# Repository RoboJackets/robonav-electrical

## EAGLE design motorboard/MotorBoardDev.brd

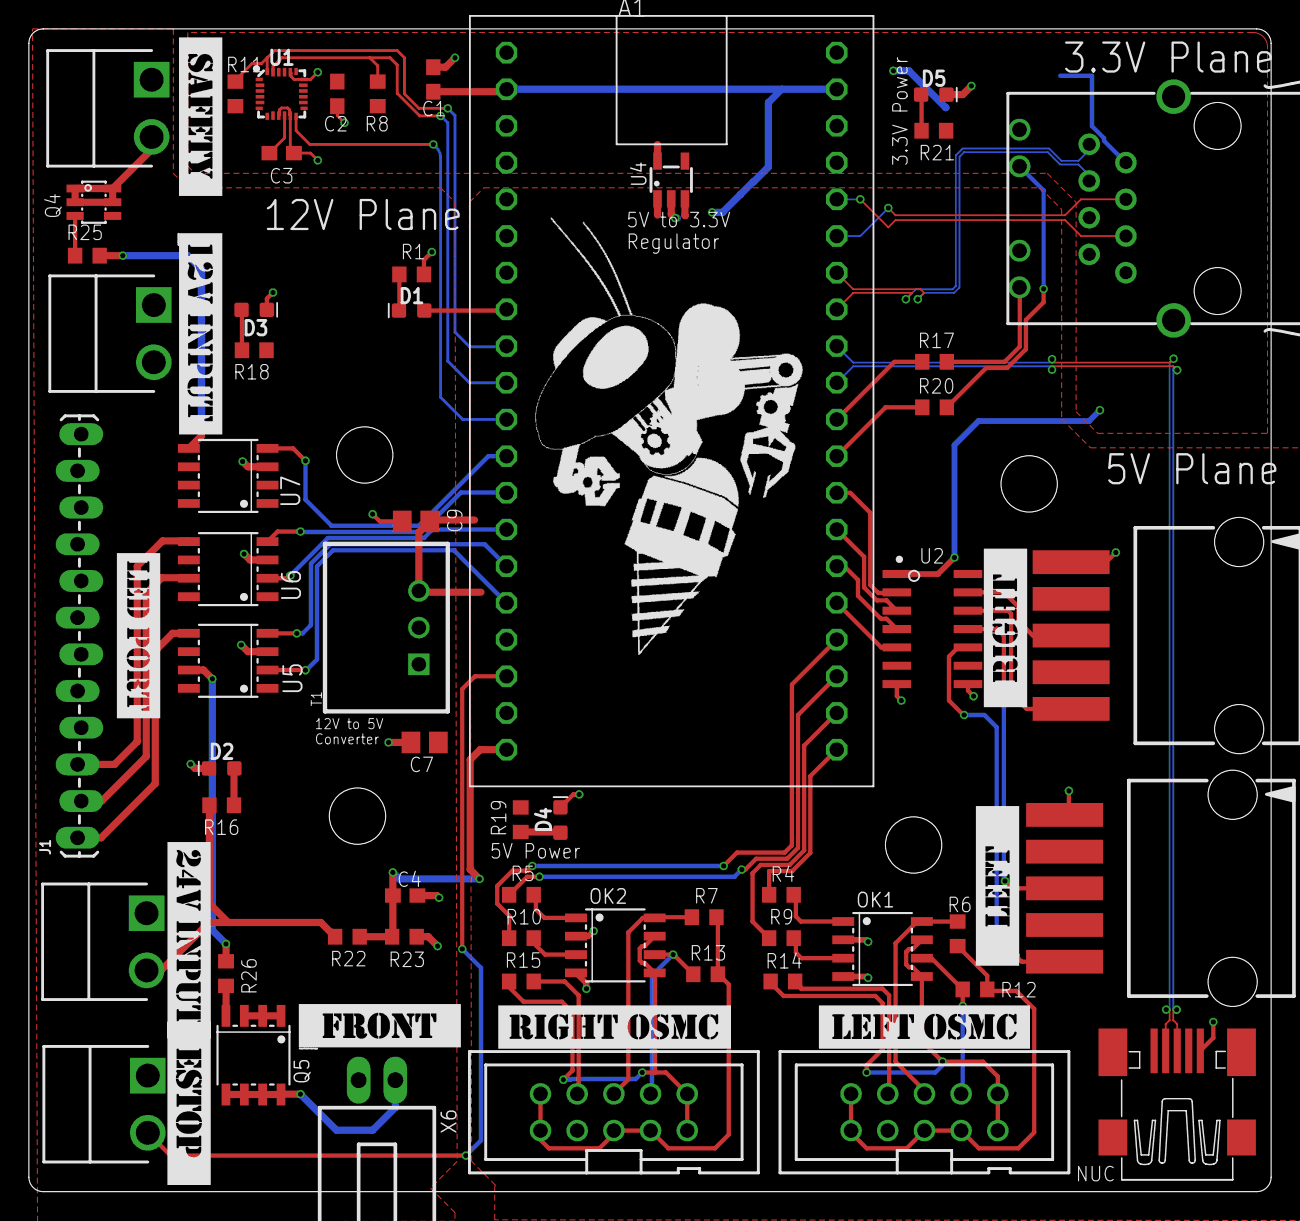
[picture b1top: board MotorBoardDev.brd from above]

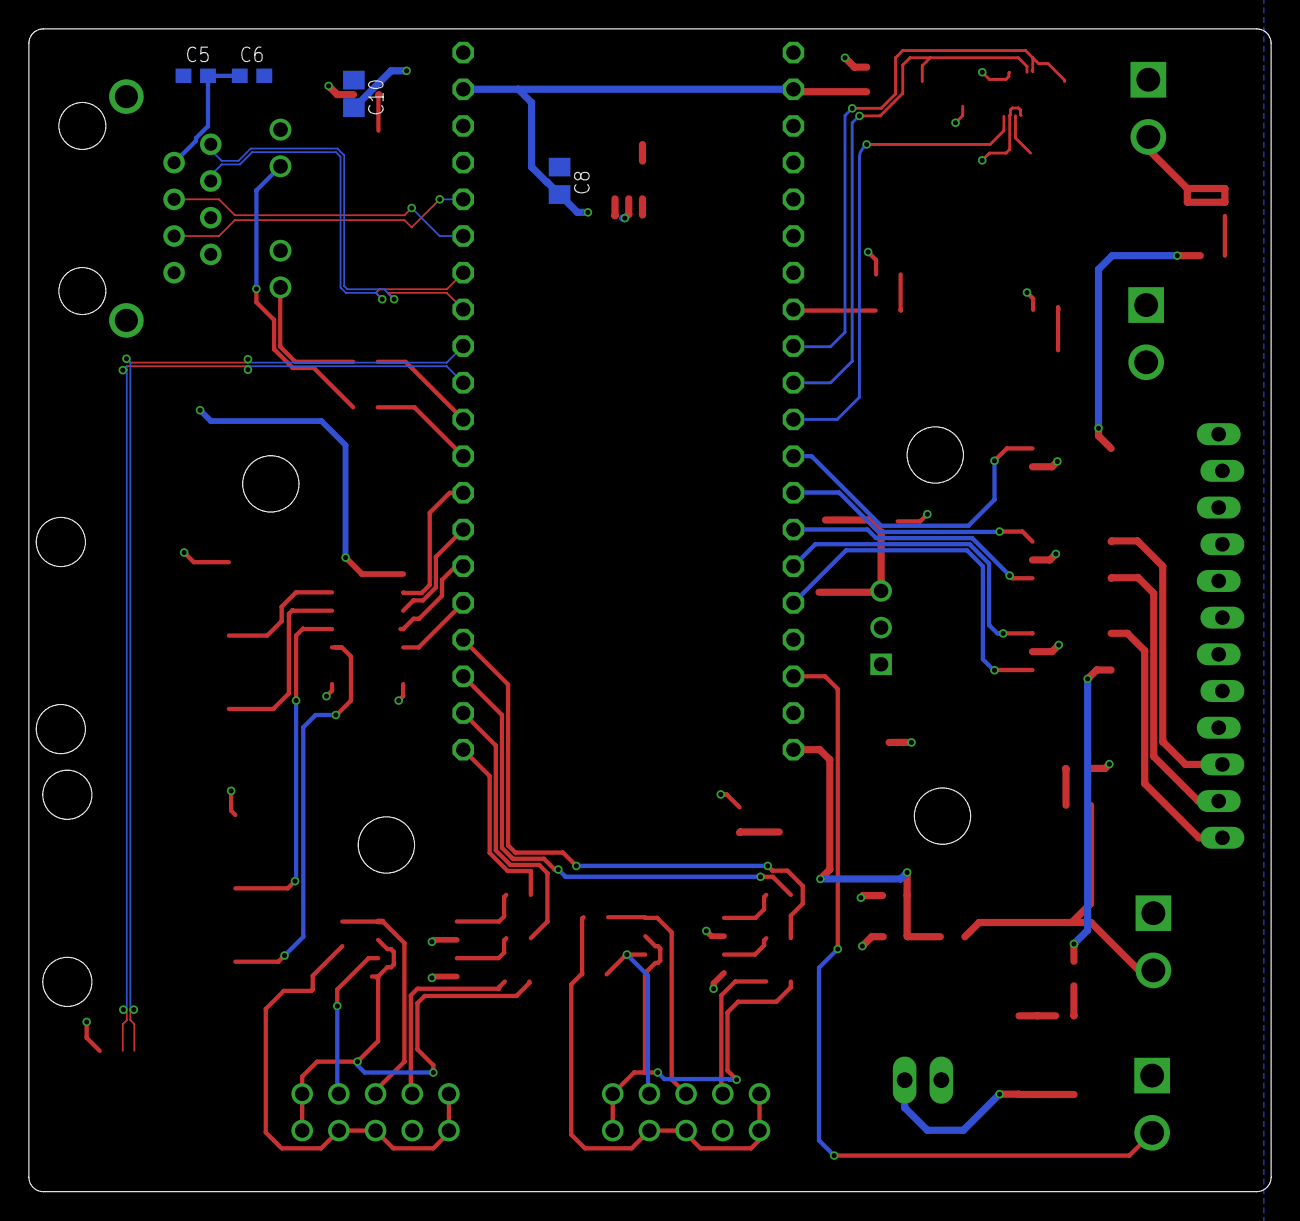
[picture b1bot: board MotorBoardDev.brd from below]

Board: 2 copper layers, 86.0 x 80.5 mm, 77 parts (4 on the bottom side), 67 nets.

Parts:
A1: MBED1768; SPARKFUN-BOARDS_DIL40_0.9
C1, C2, C3, C4, C5, C6: 0.1uF; C0603
C7, C8, C9: 10uF; C0805
C10: 1uF; C0805
D1, D3: BLUE; LED-0603
D2: Yellow; LED-0603
D4, D5: GREEN; LED-0603
J1: Under Glow; 1X12_LOCK_LONGPADS
J2, J3, J4, J5: B2PS-VH(LF)(SN); B2PS-CENTERED
OK1, OK2: MOCD208M; SOIC08-FAIRCHILD
Q4: STT4P3LLH6; SOT23-6
Q5: RRH100P03GZETB; SOIC-8
R1, R21: 100; R0603
R4, R5, R9, R10: 30; R0603
R6, R7, R8, R11, R12, R13, R22: 4.7k; R0603
R14, R15, R18: 1k; R0603
R16: 1.8k; R0603
R17, R20: 500; R0603
R19: 200; R0603
R23: 510; R0603
R25, R26: 2.7k; R0603
T1: R-78E5.0-1.0; R-78E
U1: 9DoF IMU; QFN24-3X3
U2: TXB0104DR; D14
U4: TLV70233DBVR; SOT-23-5
U5, U6, U7: TC4427ACOA713; SOIC-8
U$1, U$2, U$3, U$4: STANDOFF-HOLE
U$5: 12VINPUT
U$6: 24VINPUT
U$7: LEFTOSMC
U$8: RIGHTOSMC
U$9: LEDPORT
U$10: ROBOBUZZ_1.4X
U$11: ESTOP
U$12: SAFETY
U$13: LEFT
U$14: RIGHT
U$15: FRONT
X1: MINI-USB_SHIELD5P4-32005-400; 32005-400
X2, X5: C-GRID-05-15-91; 15-91-05
X3, X4: 2510-; PAK100/2500-10
X6: C-GRID-02-70553; 70553-02
X7: SI-50170

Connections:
3V3_LED_R: D5.A, R21.1
5V_LED_R: D4.A, R19.1
12V_LED_R: D3.A, R18.1
24V_LED_R: D2.A, R16.1
+3V3: A1.40, C2.1, C5.1, C6.1, C10.1, R8.2, R11.2, R21.2, U1.1, U1.8, U1.13, U1.22, U2.1, U4.5, X7.2, X7.5
+5V: A1.2, A1.39, C1.1, C8.1, C9.1, R19.2, T1.3, U2.14, U4.1, U4.3, X1.1, X2.4, X5.4
+12V: C7.1, J3.2, Q4.4, Q5.1, Q5.2, Q5.3, R18.2, T1.1, U5.6, U6.6, U7.6
+24V: J4.2, R16.2, R22.2
BATTIN: A1.20, C4.1, R22.1, R23.2
BLUE_3V3: A1.15, U5.4
BLUE_OUT: J1.1, U5.5
D_N: A1.32, X1.2
D_P: A1.31, X1.3
ESTOP: A1.18, J5.2
ETH_LED1: A1.30, R17.1
ETH_LED2: A1.29, R20.1
FRONT_HDR: Q5.5, Q5.6, Q5.7, Q5.8, X6.1
FRONT_LIGHT: R26.1, U5.7
FRONT_LIGHT_3V3: A1.16, U5.2
FRONT_R: Q5.4, R26.2
GND: A1.1, C1.2, C2.2, C3.2, C4.2, C5.2, C6.2, C7.2, C8.2, C9.2, C10.2, D2.C, D3.C, D4.C, D5.C, J1.4, J1.5, J1.6, J1.10, J1.11, J1.12, J2.1, J3.1, J4.1, J5.1, OK1.2, OK1.4, OK2.2, OK2.4, R1.1, R23.1, T1.2, U1.9, U1.11, U1.18, U1.20, U2.7, U2.8, U4.2, U5.3, U6.3, U7.3, X1.5, X2.1, X5.1, X6.2, X7.C1, X7.C2, X7.S1, X7.S2
GREEN_3V3: A1.14, U6.2
GREEN_OUT: J1.2, U6.7
GYRO_INT: A1.11, U1.12
INDICATOR_LED: A1.8, D1.A
INDI_LED_R: D1.C, R1.2
L+12V: R6.2, R12.2, X3.1, X3.2, X3.5, X3.7
LALI: OK1.8, R6.1, X3.6
LALI_CTRL: A1.21, R4.1
LBLI: OK1.6, R12.1, X3.8
LBLI_CTRL: A1.22, R9.1
LDISABLE: R14.2, X3.4
LEA: U2.11, X5.3
LEA3: A1.26, U2.4
LEB: U2.10, X5.5
LEB3: A1.25, U2.5
LGND: OK1.5, OK1.7, R14.1, X3.9, X3.10
unnamed: R17.2, X7.A1
unnamed: R20.2, X7.A2
R+12V: R7.2, R13.2, X4.1, X4.2, X4.5, X4.7
RALI: OK2.8, R7.1, X4.6
RALI_CTRL: A1.23, R5.1
RBLI: OK2.6, R13.1, X4.8
RBLI_CTRL: A1.24, R10.1
RDISABLE: R15.2, X4.4
RD_N: A1.36, X7.6
RD_P: A1.35, X7.4
REA: U2.13, X2.3
REA3: A1.28, U2.2
REB: U2.12, X2.5
REB3: A1.27, U2.3
RED_3V3: A1.13, U6.4
RED_OUT: J1.3, U6.5
REGOUT_C: C3.1, U1.10
RGND: OK2.5, OK2.7, R15.1, X4.9, X4.10
R_OK3A: OK1.1, R4.2
R_OK3B: OK1.3, R9.2
R_OK4A: OK2.1, R5.2
R_OK4B: OK2.3, R10.2
SAFETY_HRD: J2.2, Q4.1, Q4.2, Q4.5, Q4.6
SAFETY_LIGHT: R25.1, U7.5
SAFETY_LIGHT_3V3: A1.12, U7.4
SAFETY_R: Q4.3, R25.2
SCL: A1.10, R8.1, U1.23
SDA: A1.9, R11.1, U1.24
TD_N: A1.34, X7.3
TD_P: A1.33, X7.1

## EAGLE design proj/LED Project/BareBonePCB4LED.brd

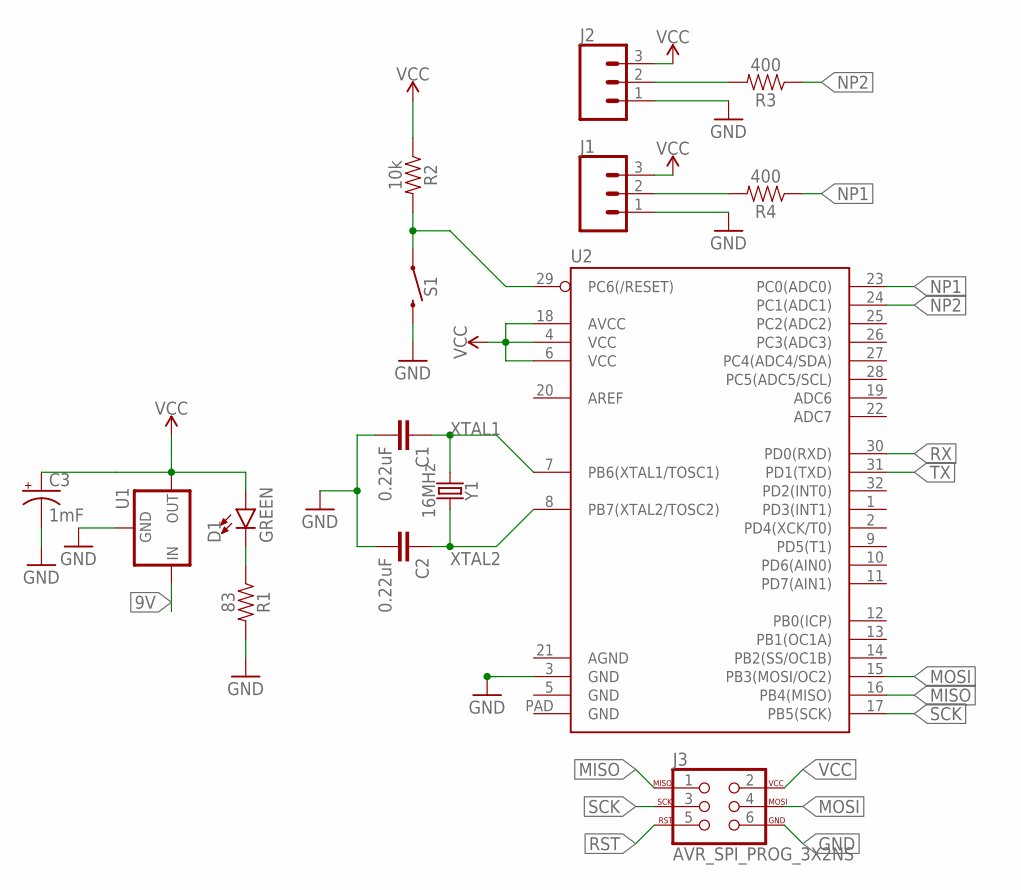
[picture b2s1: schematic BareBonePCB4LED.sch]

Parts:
C1, C2: 0.22uF; 0603
C3: 1mF; CPOL-RADIAL-5MM-10MM
D1: GREEN; LED-0603
J1, J2: CONN_03; 1X03
J3: AVR_SPI_PROG_3X2NS; 2X3-NS
R1: 83; 0603
R2: 10k; 0603
R3, R4: 400; 0603
S1: MOMENTARY-SWITCH-SPST-PTH-6.0MM-KIT; TACTILE_SWITCH_PTH_6.0MM_KIT
U1: R-78E5.0-1.0; DC-DC_CONVERTER_78XX
U2: ATMEGA328P_MLFMLF32; MLF32-PAD
Y1: 16MHz; HC49US

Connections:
9V: U1.VIN (IN)
DATA1: J1.2, R4.2
DATA2: J2.2, R3.2
GND: C1.2, C2.2, C3.-, J1.1, J2.1, J3.6, R1.2, S1.3 (2), U1.GND, U2.3 (GND)
MISO: J3.1, U2.16 (PB4(MISO))
MOSI: J3.4, U2.15 (PB3(MOSI/OC2))
unnamed: D1.C, R1.1
NP1: R4.1, U2.23 (PC0(ADC0))
NP2: R3.1, U2.24 (PC1(ADC1))
RST: J3.5, R2.2, S1.1, U2.29 (PC6(/RESET))
RX: U2.30 (PD0(RXD))
SCK: J3.3, U2.17 (PB5(SCK))
TX: U2.31 (PD1(TXD))
VCC: C3.+, D1.A, J1.3, J2.3, J3.2, R2.1, U1.VOUT (OUT), U2.4 (VCC), U2.6 (VCC), U2.18 (AVCC)
XTAL1: C1.1, U2.7 (PB6(XTAL1/TOSC1)), Y1.1
XTAL2: C2.1, U2.8 (PB7(XTAL2/TOSC2)), Y1.2

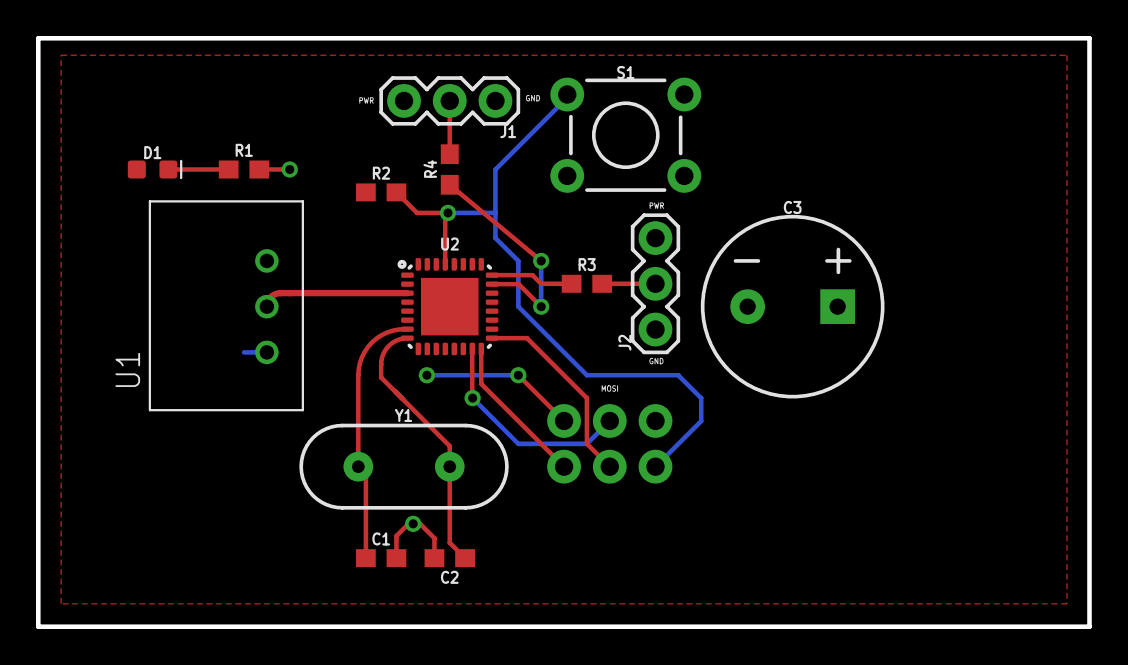
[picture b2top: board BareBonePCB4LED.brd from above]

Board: 2 copper layers, 58.4 x 32.7 mm, 15 parts (0 on the bottom side), 13 nets.

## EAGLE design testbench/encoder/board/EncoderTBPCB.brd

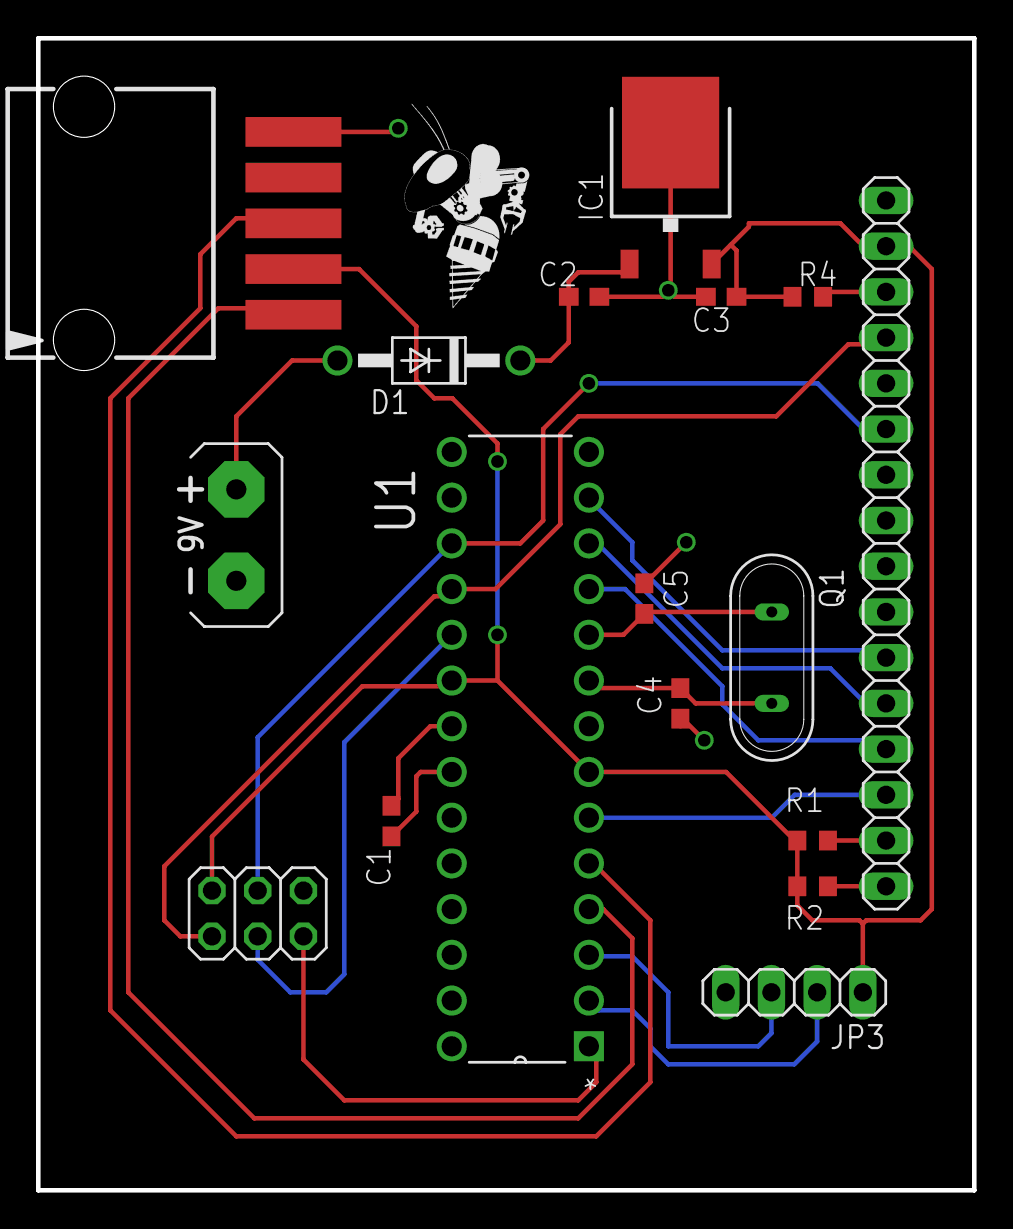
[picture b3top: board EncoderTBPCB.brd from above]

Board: 2 copper layers, 52.0 x 64.0 mm, 18 parts (0 on the bottom side), 21 nets.

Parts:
C1, C3: 0.1uF; C0603
C2: 0.33uF; C0603
C4, C5: 22pF; C0603
D1: 1N4004; DO41-10
G1: AB9V
IC1: 7805DT; TO252
JP1: 2X03
JP2: 1X16
JP3: 1X04
Q1: 16MHz; QS
R1: 220; R0603
R2: 200; R0603
R4: 850; R0603
U1: ATMEGA328P-PU; DIP254P762X457-28
U$1: ROBOBUZZ_0.6X
X1: C-GRID-05-15-91; 15-91-05

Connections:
CRYSTAL: C4.1, Q1.2, U1.9
ENPA: U1.4, X1.1
ENPB: U1.5, X1.3
GND: C1.2, C2.2, C3.2, C4.2, C5.2, G1.-, IC1.3, JP1.6, JP2.1, JP2.5, JP2.16, JP3.4, R2.2, U1.8, U1.22, X1.5
unnamed: JP2.15, R1.2
unnamed: C5.1, Q1.1, U1.10
unnamed: C1.1, U1.21
unnamed: D1.A, G1.+
unnamed: C2.1, D1.C, IC1.1
P4T14: JP2.14, U1.6
P5T13: JP2.13, U1.11
P6T12: JP2.12, U1.12
P7T11: JP2.11, U1.13
PB3: JP1.4, JP2.6, U1.17
PB4: JP1.1, JP2.4, U1.18
PB5: JP1.3, U1.19
PC6: JP1.5, U1.1
RX: JP3.2, U1.2
TX: JP3.3, U1.3
VDD: C3.1, IC1.2, JP1.2, JP2.2, JP3.1, R1.1, R2.1, R4.1, U1.7, U1.20, X1.2
VO: JP2.3, R4.2

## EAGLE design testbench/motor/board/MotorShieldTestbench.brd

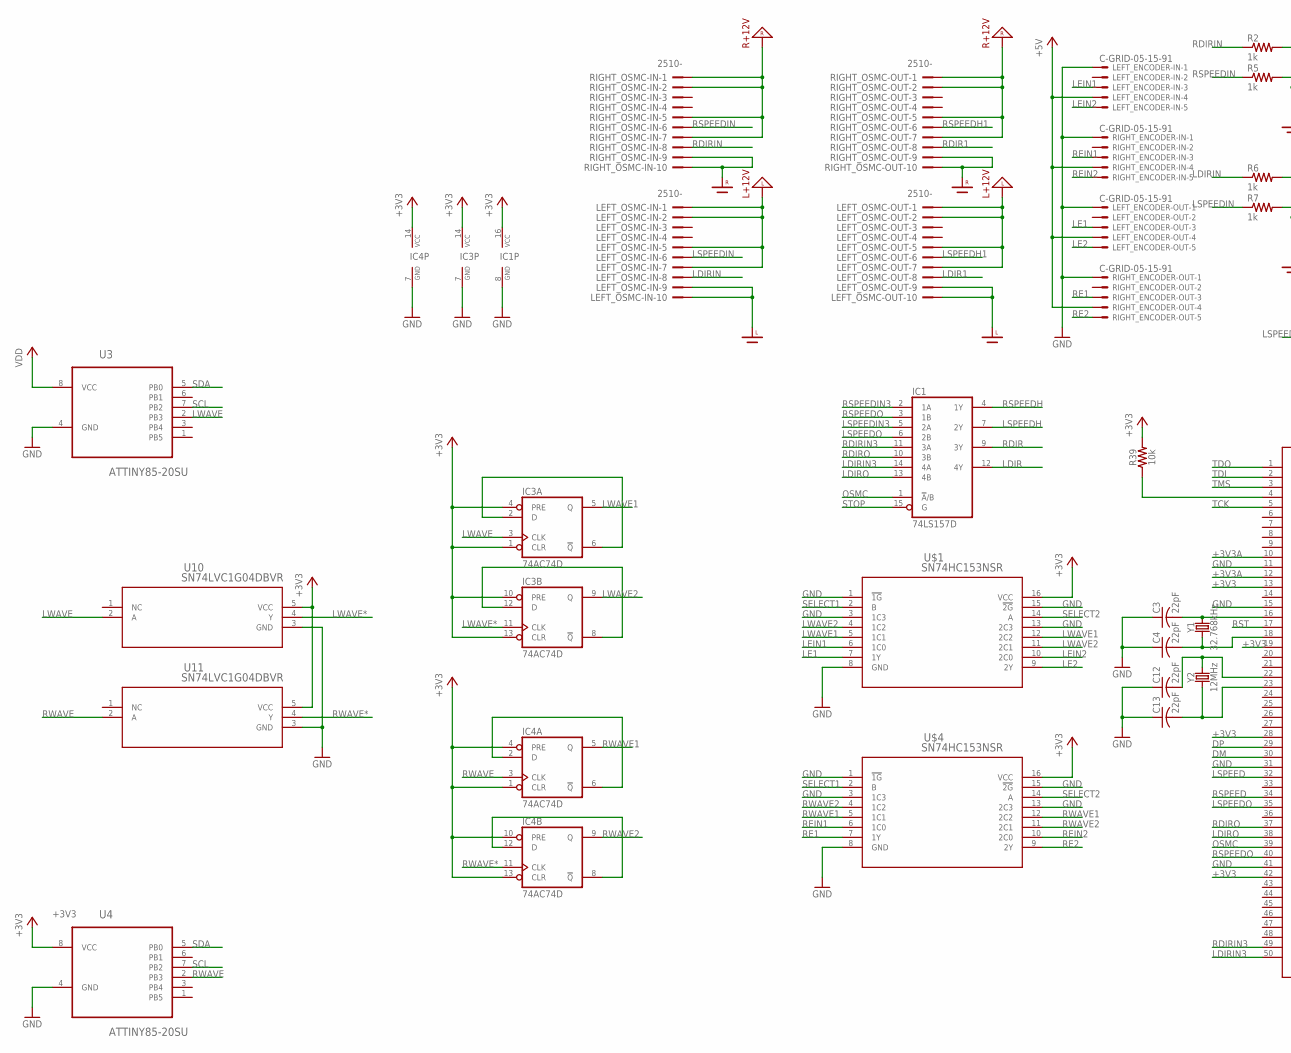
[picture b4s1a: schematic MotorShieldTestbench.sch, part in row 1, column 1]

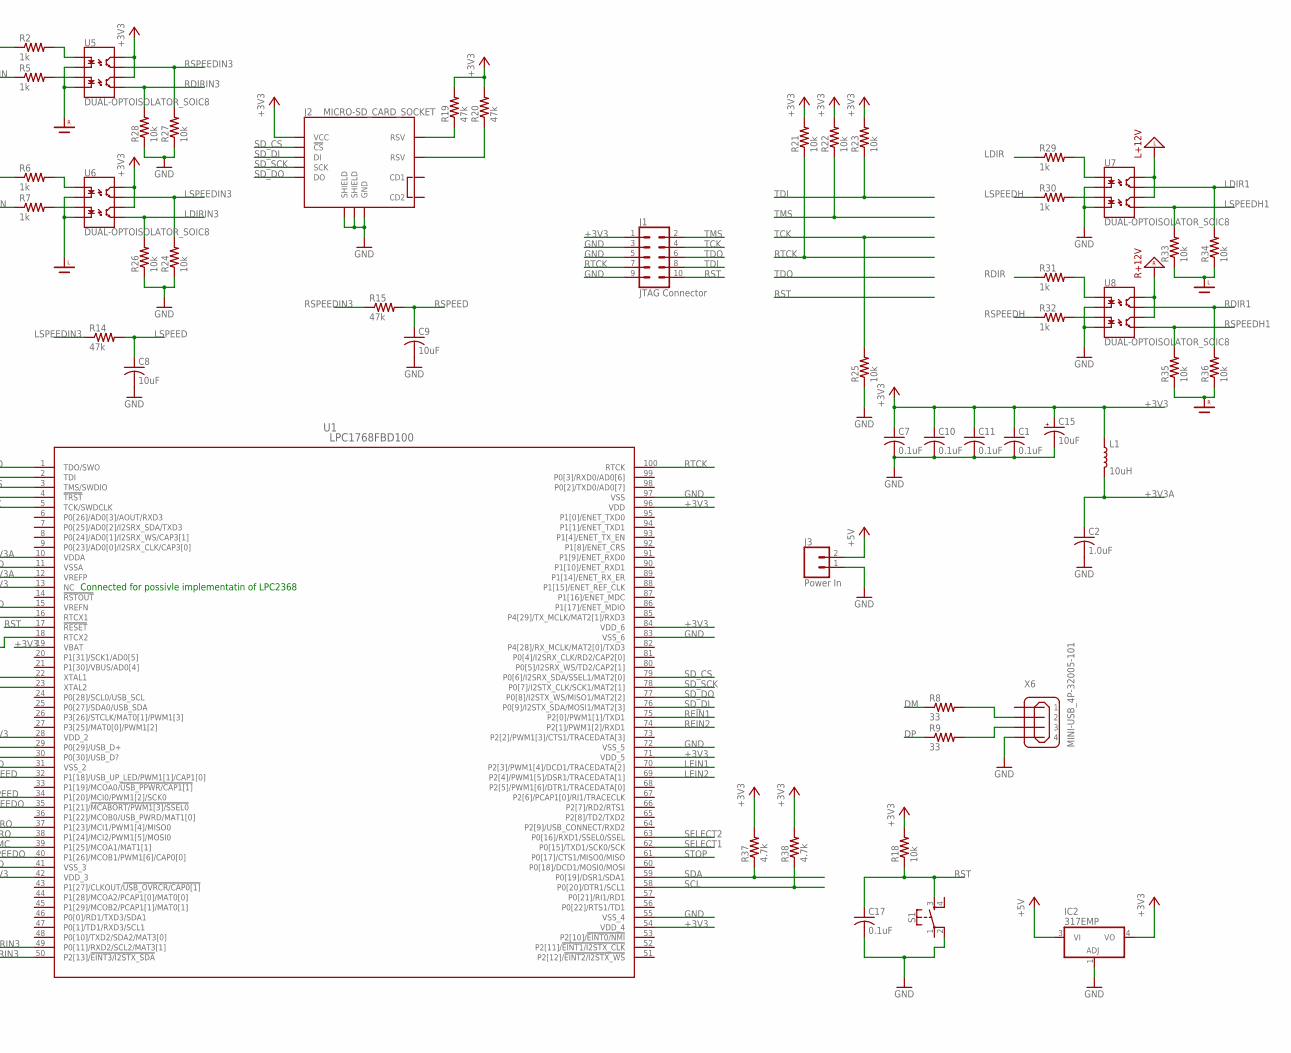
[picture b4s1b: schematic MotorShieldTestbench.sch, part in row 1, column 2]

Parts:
C1, C7, C10, C11, C17: 0.1uF; C0603
C2: 1.0uF; C0603
C3, C4, C12, C13: 22pF; C0603
C8, C9: 10uF; C0603
C15: 10uF; 0603-POLAR
IC1: 74LS157D; SO16
IC2: 317EMP; SOT223
IC3, IC4: 74AC74D; SO14
J1: JTAG Connector; 2X5-SHROUDED
J2: MICRO-SD_CARD_SOCKET; MICRO-SD-SOCKET
J3: Power In; MOLEX-1X2
L1: 10uH; 0603
LEFT_ENCODER-IN: C-GRID-05-15-91; 15-91-05
LEFT_ENCODER-OUT: C-GRID-05-15-91; 15-91-05
LEFT_OSMC-IN: 2510-; PAK100/2500-10
LEFT_OSMC-OUT: 2510-; PAK100/2500-10
R2, R5, R6, R7, R29, R30, R31, R32: 1k; R0603
R8, R9: 33; R0603
R14, R15, R19, R20: 47k; R0603
R18, R21, R22, R23, R24, R25, R26, R27, R28, R33, R34, R35, R36: 10k; R0603
R37, R38: 4.7k; R0603
R39: 10k; 0603
RIGHT_ENCODER-IN: C-GRID-05-15-91; 15-91-05
RIGHT_ENCODER-OUT: C-GRID-05-15-91; 15-91-05
RIGHT_OSMC-IN: 2510-; PAK100/2500-10
RIGHT_OSMC-OUT: 2510-; PAK100/2500-10
S1: MOMENTARY-SWITCH-SPST-2-SMD-5.2MM; TACTILE_SWITCH_SMD_5.2MM
U1: LPC1768FBD100; SOT407-1
U3, U4: ATTINY85-20SU; SOIC127P798X216-8N
U5, U6, U7, U8: DUAL-OPTOISOLATOR_SOIC8; SO08
U10, U11: SN74LVC1G04DBVR; DBV5
U$1, U$4: SN74HC153NSR; NS16
X6: MINI-USB_4P-32005-101; 32005-101
Y1: 32.768kHz; CRYSTAL-SMD-3.2X1.5MM
Y2: 12MHz; CRYSTAL-SMD-5X3.2-4PAD

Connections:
+3V3: C1.1, C7.1, C10.1, C11.1, C15.+, IC1.16 (VCC), IC2.4 (VO), IC3.1 (CLR), IC3.4 (PRE), IC3.10 (PRE), IC3.13 (CLR), IC3.14 (VCC), IC4.1 (CLR), IC4.4 (PRE), IC4.10 (PRE), IC4.13 (CLR), IC4.14 (VCC), J1.1, J2.VCC, L1.1, R18.2, R19.2, R20.2, R21.2, R22.2, R23.2, R37.2, R38.2, R39.2, U1.13 (NC), U1.19 (VBAT), U1.28 (VDD_2), U1.42 (VDD_3), U1.54 (VDD_4), U1.71 (VDD_5), U1.84 (VDD_6), U1.96 (VDD), U3.8 (VCC), U4.8 (VCC), U5.6 (CL2), U5.8 (CL1), U6.6 (CL2), U6.8 (CL1), U10.5 (VCC), U11.5 (VCC), U$1.16 (VCC), U$4.16 (VCC)
+3V3A: C2.1, L1.2, U1.10 (VDDA), U1.12 (VREFP)
+5V: IC2.3 (VI), J3.2, LEFT_ENCODER-IN.4, LEFT_ENCODER-OUT.4, RIGHT_ENCODER-IN.4, RIGHT_ENCODER-OUT.4
DM: R8.1, U1.30 (P0[30]/USB_D?)
DP: R9.1, U1.29 (P0[29]/USB_D+)
GND: C1.2, C2.2, C3.1, C4.1, C7.2, C8.2, C9.2, C10.2, C11.2, C12.1, C13.1, C15.-, C17.2, IC1.8 (GND), IC2.1 (ADJ), IC3.7 (GND), IC4.7 (GND), J1.3, J1.5, J1.9, J2.GND, J2.GND1 (SHIELD), J2.GND3 (SHIELD), J3.1, LEFT_ENCODER-IN.1, LEFT_ENCODER-OUT.1, R24.1, R25.1, R26.1, R27.1, R28.1, RIGHT_ENCODER-IN.1, RIGHT_ENCODER-OUT.1, S1.2, U1.11 (VSSA), U1.15 (VREFN), U1.31 (VSS_2), U1.41 (VSS_3), U1.55 (VSS_4), U1.72 (VSS_5), U1.83 (VSS_6), U1.97 (VSS), U3.4 (GND), U4.4 (GND), U7.2 (C1), U7.4 (C2), U8.2 (C1), U8.4 (C2), U10.3 (GND), U11.3 (GND), U$1.1 (!1G), U$1.3 (1C3), U$1.8 (GND), U$1.13 (2C3), U$1.15 (!2G), U$4.1 (!1G), U$4.3 (1C3), U$4.8 (GND), U$4.13 (2C3), U$4.15 (!2G), X6.4
L+12V: LEFT_OSMC-IN.1, LEFT_OSMC-IN.2, LEFT_OSMC-IN.5, LEFT_OSMC-IN.7, LEFT_OSMC-OUT.1, LEFT_OSMC-OUT.2, LEFT_OSMC-OUT.5, LEFT_OSMC-OUT.7, U7.6 (CL2), U7.8 (CL1)
LDIR: IC1.12 (4Y), R29.1
LDIR1: LEFT_OSMC-OUT.8, R34.2, U7.7 (EM1)
LDIRIN: LEFT_OSMC-IN.8, R6.1
LDIRIN3: IC1.14 (4A), R26.2, U1.50 (P2[13]/!EINT3/I2STX_SDA), U6.5 (EM2)
LDIRO: IC1.13 (4B), U1.38 (P1[24]/MCI2/PWM1[5]/MOSI0)
LE1: LEFT_ENCODER-OUT.3, U$1.7 (1Y)
LE2: LEFT_ENCODER-OUT.5, U$1.9 (2Y)
LEIN1: LEFT_ENCODER-IN.3, U1.70 (P2[3]/PWM1[4]/DCD1/TRACEDATA[2]), U$1.6 (1C0)
LEIN2: LEFT_ENCODER-IN.5, U1.69 (P2[4]/PWM1[5]/DSR1/TRACEDATA[1]), U$1.10 (2C0)
LGND: LEFT_OSMC-IN.9, LEFT_OSMC-IN.10, LEFT_OSMC-OUT.9, LEFT_OSMC-OUT.10, R33.1, R34.1, U6.2 (C1), U6.4 (C2)
LSPEED: C8.1, R14.2, U1.32 (P1[18]/USB_UP_LED/PWM1[1]/CAP1[0])
LSPEEDH: IC1.7 (2Y), R30.1
LSPEEDH1: LEFT_OSMC-OUT.6, R33.2, U7.5 (EM2)
LSPEEDIN: LEFT_OSMC-IN.6, R7.1
LSPEEDIN3: IC1.5 (2A), R14.1, R24.2, U6.7 (EM1)
LSPEEDO: IC1.6 (2B), U1.35 (P1[21]/!MCABORT/PWM1[3]/SSEL0)
LWAVE: IC3.3 (CLK), U3.2 (PB3), U10.2 (A)
LWAVE1: IC3.5 (Q), U$1.5 (1C1), U$1.12 (2C2)
LWAVE2: IC3.9 (Q), U$1.4 (1C2), U$1.11 (2C1)
LWAVE*: IC3.11 (CLK), U10.4 (Y)
unnamed: IC3.2 (D), IC3.6 (!Q)
unnamed: IC3.8 (!Q), IC3.12 (D)
unnamed: IC4.2 (D), IC4.6 (!Q)
unnamed: IC4.8 (!Q), IC4.12 (D)
unnamed: J2.RSV1 (RSV), R19.1
unnamed: J2.RSV2 (RSV), R20.1
unnamed: R7.2, U6.3 (A2)
unnamed: R9.2, X6.3
unnamed: R5.2, U5.3 (A2)
unnamed: C4.2, U1.18 (RTCX2), Y1.P$1 (1)
unnamed: C3.2, U1.16 (RTCX1), Y1.P$2 (2)
unnamed: C13.2, U1.23 (XTAL2), Y2.1
unnamed: C12.2, U1.22 (XTAL1), Y2.3 (2)
unnamed: R2.2, U5.1 (A1)
unnamed: R8.2, X6.2
unnamed: R6.2, U6.1 (A1)
unnamed: R29.2, U7.1 (A1)
unnamed: R30.2, U7.3 (A2)
unnamed: R39.1, U1.4 (!TRST)
unnamed: R31.2, U8.1 (A1)
unnamed: R32.2, U8.3 (A2)
OSMC: IC1.1 (!A!/B), U1.39 (P1[25]/MCOA1/MAT1[1])
R+12V: RIGHT_OSMC-IN.1, RIGHT_OSMC-IN.2, RIGHT_OSMC-IN.5, RIGHT_OSMC-IN.7, RIGHT_OSMC-OUT.1, RIGHT_OSMC-OUT.2, RIGHT_OSMC-OUT.5, RIGHT_OSMC-OUT.7, U8.6 (CL2), U8.8 (CL1)
RDIR: IC1.9 (3Y), R31.1
RDIR1: R36.2, RIGHT_OSMC-OUT.8, U8.7 (EM1)
RDIRIN: R2.1, RIGHT_OSMC-IN.8
RDIRIN3: IC1.11 (3A), R28.2, U1.49 (P0[11]/RXD2/SCL2/MAT3[1]), U5.5 (EM2)
RDIRO: IC1.10 (3B), U1.37 (P1[23]/MCI1/PWM1[4]/MISO0)
RE1: RIGHT_ENCODER-OUT.3, U$4.7 (1Y)
RE2: RIGHT_ENCODER-OUT.5, U$4.9 (2Y)
REIN1: RIGHT_ENCODER-IN.3, U1.75 (P2[0]/PWM1[1]/TXD1), U$4.6 (1C0)
REIN2: RIGHT_ENCODER-IN.5, U1.74 (P2[1]/PWM1[2]/RXD1), U$4.10 (2C0)
RGND: R35.1, R36.1, RIGHT_OSMC-IN.9, RIGHT_OSMC-IN.10, RIGHT_OSMC-OUT.9, RIGHT_OSMC-OUT.10, U5.2 (C1), U5.4 (C2)
RSPEED: C9.1, R15.2, U1.34 (P1[20]/MCI0/PWM1[2]/SCK0)
RSPEEDH: IC1.4 (1Y), R32.1
RSPEEDH1: R35.2, RIGHT_OSMC-OUT.6, U8.5 (EM2)
RSPEEDIN: R5.1, RIGHT_OSMC-IN.6
RSPEEDIN3: IC1.2 (1A), R15.1, R27.2, U5.7 (EM1)
RSPEEDO: IC1.3 (1B), U1.40 (P1[26]/MCOB1/PWM1[6]/CAP0[0])
RST: C17.1, J1.10, R18.1, S1.3, U1.17 (!RESET)
RTCK: J1.7, R21.1, U1.100 (RTCK)
RWAVE: IC4.3 (CLK), U4.2 (PB3), U11.2 (A)
RWAVE1: IC4.5 (Q), U$4.5 (1C1), U$4.12 (2C2)
RWAVE2: IC4.9 (Q), U$4.4 (1C2), U$4.11 (2C1)
RWAVE*: IC4.11 (CLK), U11.4 (Y)
SCL: R38.1, U1.58 (P0[20]/DTR1/SCL1), U3.7 (PB2), U4.7 (PB2)
SDA: R37.1, U1.59 (P0[19]/DSR1/SDA1), U3.5 (PB0), U4.5 (PB0)
SD_CS: J2.CS (!CS), U1.79 (P0[6]/I2SRX_SDA/SSEL1/MAT2[0])
SD_DI: J2.DI, U1.76 (P0[9]/I2STX_SDA/MOSI1/MAT2[3])
SD_DO: J2.DO, U1.77 (P0[8]/I2STX_WS/MISO1/MAT2[2])
SD_SCK: J2.SCLK (SCK), U1.78 (P0[7]/I2STX_CLK/SCK1/MAT2[1])
SELECT1: U1.62 (P0[15]/TXD1/SCK0/SCK), U$1.2 (B), U$4.2 (B)
SELECT2: U1.63 (P0[16]/RXD1/SSEL0/SSEL), U$1.14 (A), U$4.14 (A)
STOP: IC1.15 (G), U1.61 (P0[17]/CTS1/MISO0/MISO)
TCK: J1.4, R25.2, U1.5 (TCK/SWDCLK)
TDI: J1.8, R23.1, U1.2 (TDI)
TDO: J1.6, U1.1 (TDO/SWO)
TMS: J1.2, R22.1, U1.3 (TMS/SWDIO)

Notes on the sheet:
Connected for possivle implementatin of LPC2368

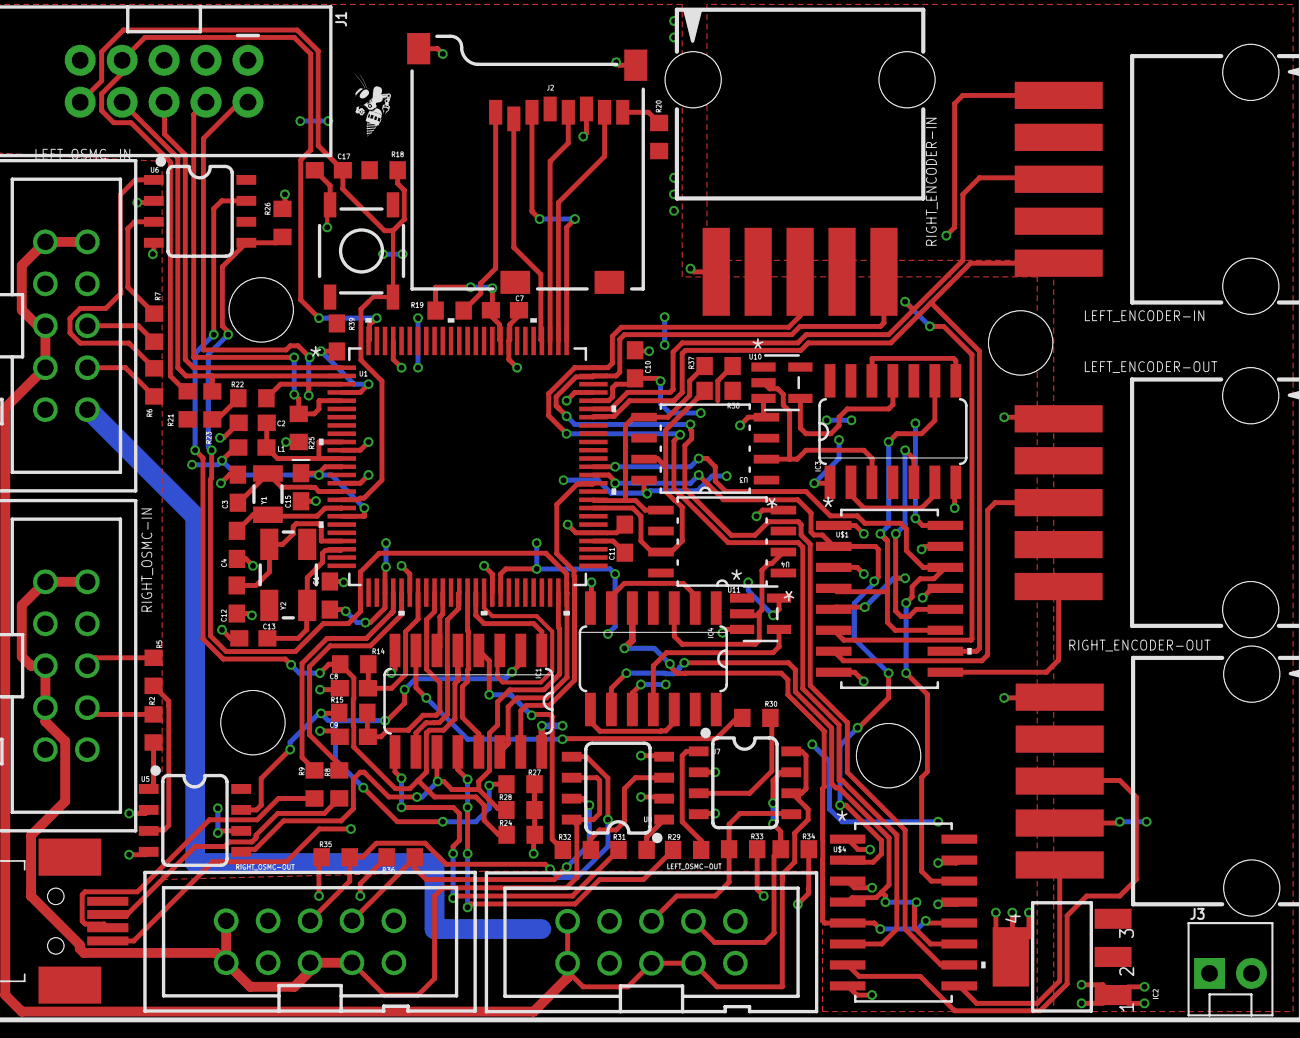
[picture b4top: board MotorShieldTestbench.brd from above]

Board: 2 copper layers, 79 parts (0 on the bottom side), 85 nets.

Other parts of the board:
22,1, 22,2, 22,3, 22,4: STANDOFF-HOLE
U$16: ROBOBUZZ_0.2X

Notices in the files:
parts and their libraries:
SparkFun-LED: Licensing: Creative Commons ShareAlike 4.0 International - https://creativecommons.org/licenses/by-sa/4.0
